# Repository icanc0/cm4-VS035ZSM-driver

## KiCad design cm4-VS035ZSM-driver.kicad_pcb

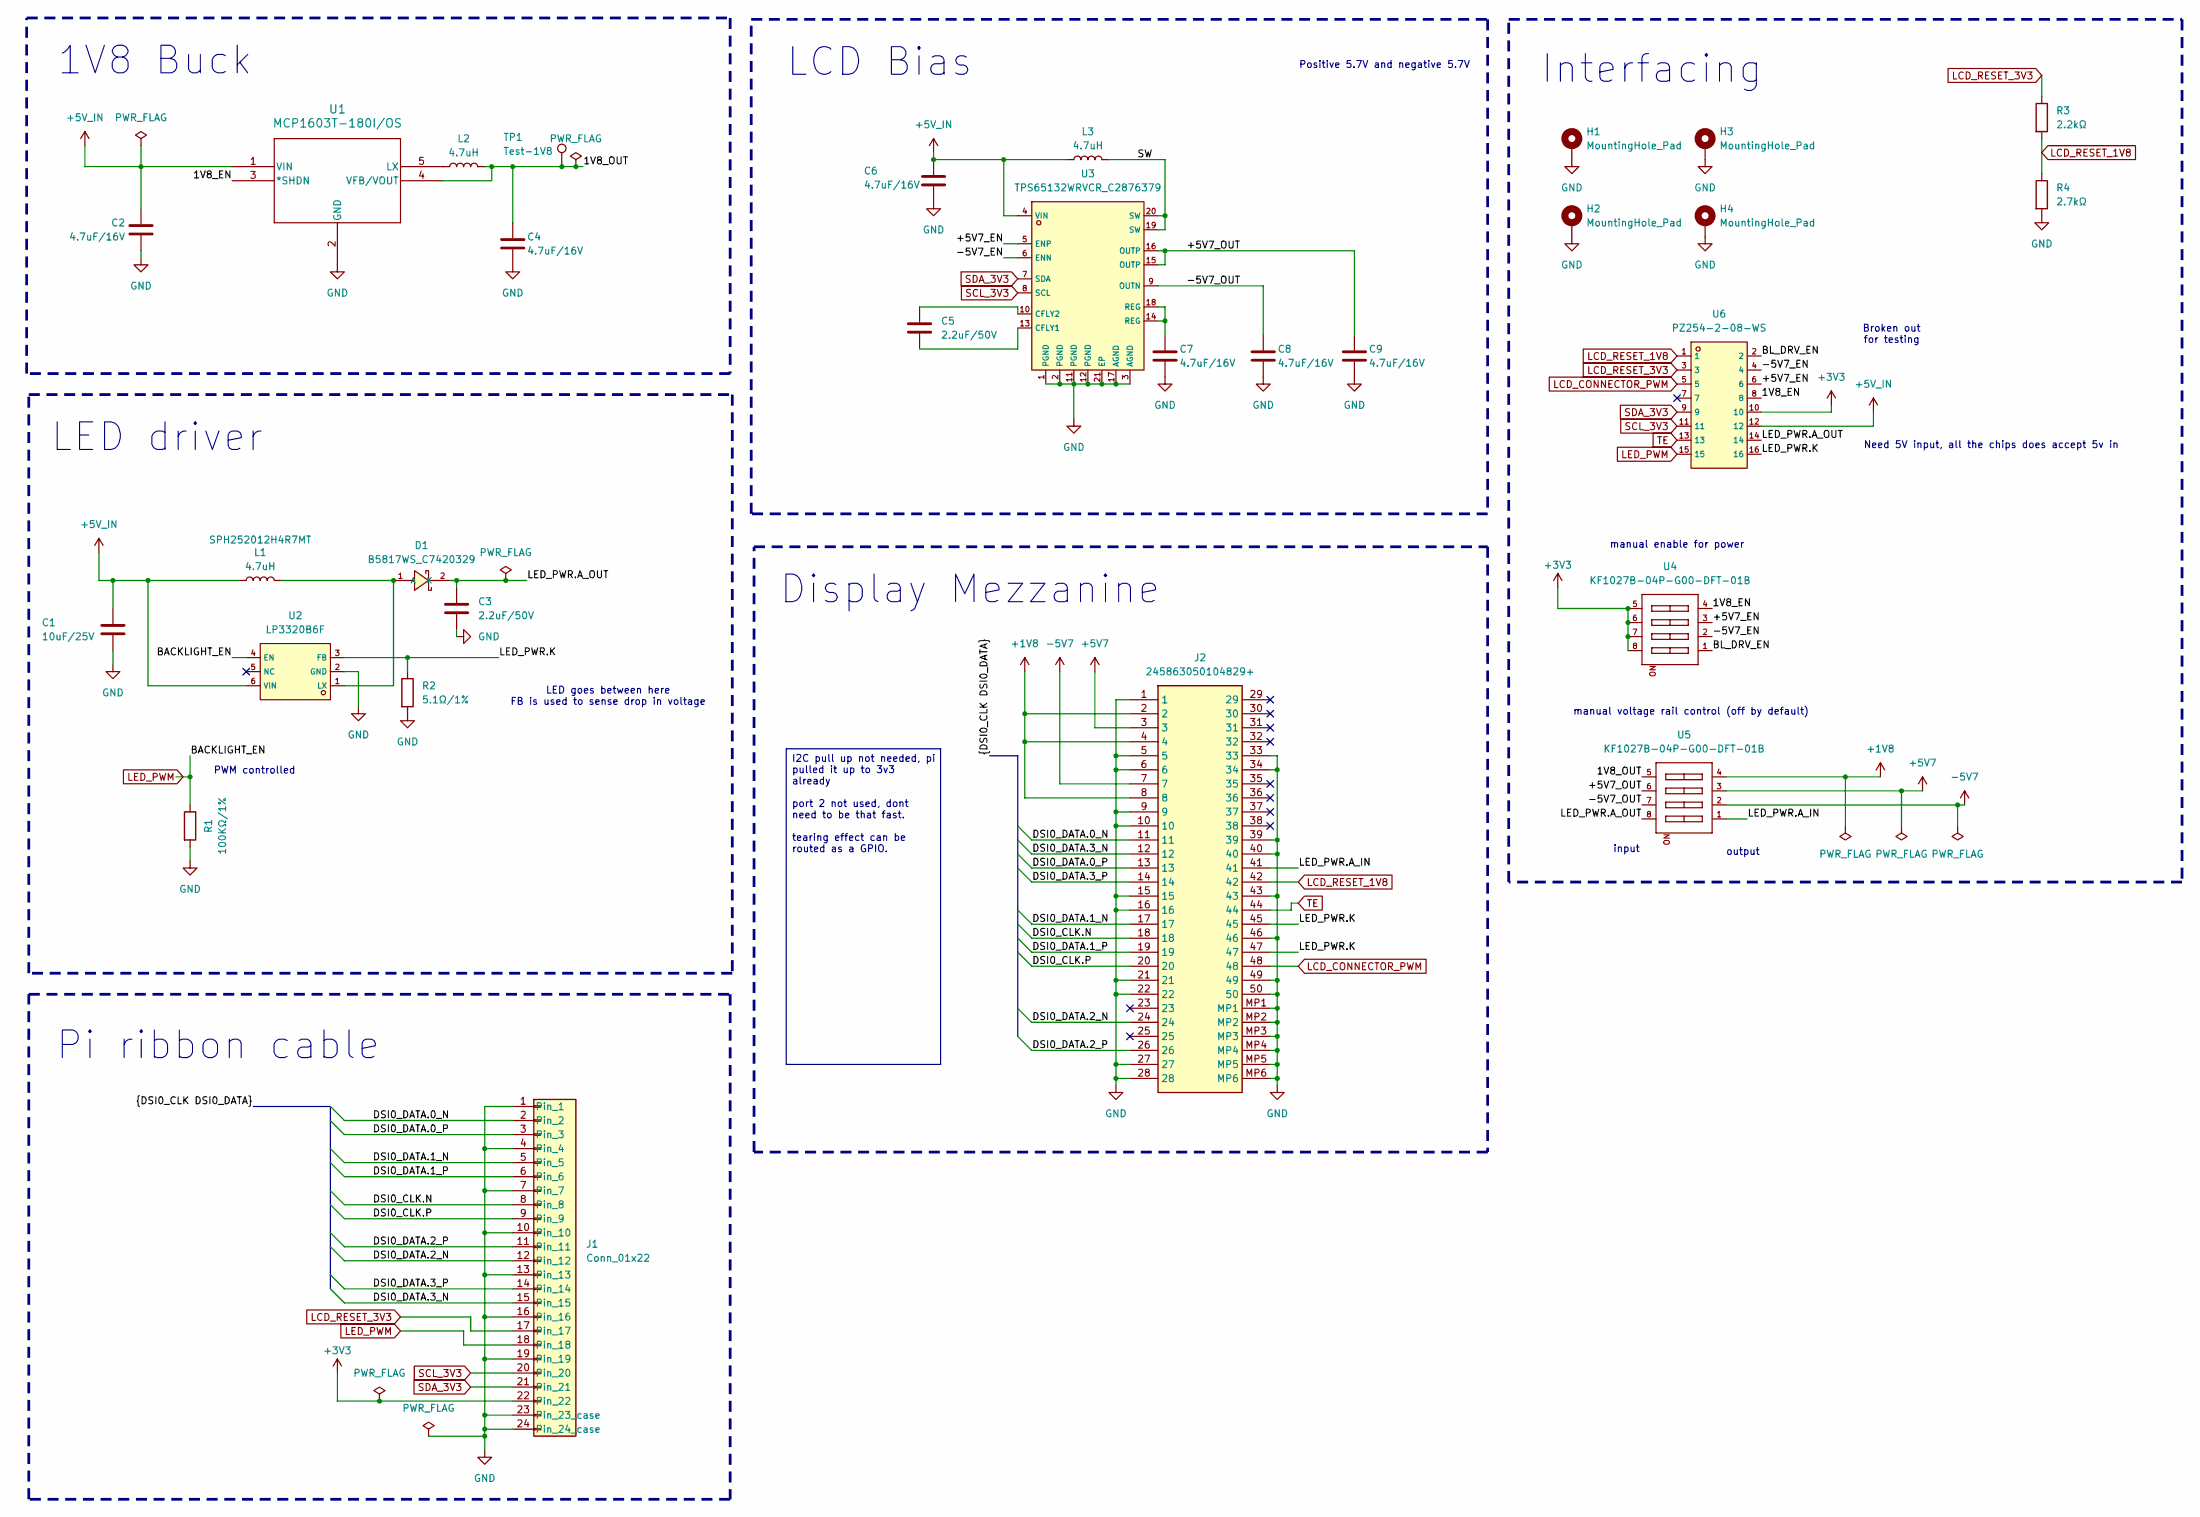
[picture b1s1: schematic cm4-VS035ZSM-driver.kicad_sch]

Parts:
C1: 10uF/25V; C_0603_1608Metric
C2, C4, C6, C7, C8, C9: 4.7uF/16V; C_0603_1608Metric
C3, C5: 2.2uF/50V; C_0805_2012Metric
D1: B5817WS_C7420329; SOD-323_L1.7-W1.3-LS2.5-FD; LCSC C7420329
H1, H2, H3, H4: MountingHole_Pad; MountingHole_3.2mm_M3_DIN965_Pad_TopBottom
J1: Conn_01x22; CON22_1X22_DRB_XF2C_TYC
J2: 245863050104829+; 245863050104829; Mouser Part Number 346-245863050104829+
L1, L2, L3: 4.7uH; IND-SMD_L2.5-W2.0_SPH252012
R1: 100KΩ/1%; R_0402_1005Metric
R2: 5.1Ω/1%; R_0805_2012Metric
R3: 2.2kΩ; R_0402_1005Metric
R4: 2.7kΩ; R_0603_1608Metric
TP1: Test-1V8; TestPoint_THTPad_D2.0mm_Drill1.0mm
U1: MCP1603T-180I/OS; TSOT5_MC_MCH
U2: LP3320B6F; SOT-23-6_L2.9-W1.6-P0.95-LS2.8-BL; LCSC C387699
U3: TPS65132WRVCR_C2876379; WQFN-20_L4.0-W3.0-P0.50-BL-EP; LCSC C2876379
U4, U5: KF1027B-04P-G00-DFT-01B; SW-SMD_KF1027B-04P-G00-DFT-01B; LCSC C976366
U6: PZ254-2-08-WS; HDR-SMD_16P-P2.54-H-M-R2-C8-W12.0-N; LCSC C5149358

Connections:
+1V8: J2.2, J2.4, J2.8, U5.4 (A4)
+3V3: J1.22, U4.5 (B4), U4.6 (B3), U4.7 (B2), U4.8 (B1), U6.10
+5V7: J2.3, U5.3 (A3)
+5V_IN: C1.2, C2.2, C6.1, L1.1, L3.1, U1.1 (VIN), U2.6 (VIN), U3.4 (VIN), U6.12
-5V7: J2.7, U5.2 (A2)
/1V8_EN: U1.3 (*SHDN), U4.4 (A4), U6.8
/1V8_OUT: C4.1, L2.2, TP1.1 (1_1), U1.4 (VFB/VOUT), U5.5 (B4)
/+5V7_EN: U3.5 (ENP), U4.3 (A3), U6.6
/+5V7_OUT: C9.1, U3.15 (OUTP), U3.16 (OUTP), U5.6 (B3)
/-5V7_EN: U3.6 (ENN), U4.2 (A2), U6.4
/-5V7_OUT: C8.1, U3.9 (OUTN), U5.7 (B2)
/BL_DRV_EN: U4.1 (A1), U6.2
/DSI0_CLK.N: J1.8, J2.18
/DSI0_CLK.P: J1.9, J2.20
/DSI0_DATA.0_N: J1.2, J2.11
/DSI0_DATA.0_P: J1.3, J2.13
/DSI0_DATA.1_N: J1.5, J2.17
/DSI0_DATA.1_P: J1.6, J2.19
/DSI0_DATA.2_N: J1.12, J2.24
/DSI0_DATA.2_P: J1.11, J2.26
/DSI0_DATA.3_N: J1.15, J2.12
/DSI0_DATA.3_P: J1.14, J2.14
/LED_PWR.A_IN: J2.41, U5.1 (A1)
/LED_PWR.A_OUT: C3.1, D1.2 (K), U5.8 (B1), U6.14
/LED_PWR.K: J2.45, J2.47, R2.1, U2.3 (FB), U6.16
/SW: L3.2, U3.19 (SW), U3.20 (SW)
GND: C1.1, C2.1, C3.2, C4.2, C6.2, C7.2, C8.2, C9.2, H1.1 (1_1), H2.1 (1_1), H3.1 (1_1), H4.1 (1_1), J1.1, J1.4, J1.7, J1.10, J1.13, J1.16, J1.19, J1.23 (Pin_23_case), J1.24 (Pin_24_case), J2.1, J2.5, J2.6, J2.9, J2.10, J2.15, J2.16, J2.21, J2.22, J2.27, J2.28, J2.33, J2.34, J2.39, J2.40, J2.43, J2.46, J2.49, J2.50, J2.MP1, J2.MP2, J2.MP3, J2.MP4, J2.MP5, J2.MP6, R1.2, R2.2, R4.2, U1.2 (GND), U2.2 (GND), U3.1 (PGND), U3.2 (PGND), U3.3 (AGND), U3.11 (PGND), U3.12 (PGND), U3.17 (AGND), U3.21 (EP)
LCD_CONNECTOR_PWM: J2.48, U6.5
LCD_RESET_1V8: J2.42, R3.2, R4.1, U6.1
LCD_RESET_3V3: J1.17, R3.1, U6.3
LED_PWM: J1.18, R1.1, U2.4 (EN), U6.15
unnamed: C7.1, U3.14 (REG), U3.18 (REG)
unnamed: D1.1 (A), L1.2, U2.1 (LX)
unnamed: L2.1, U1.5 (LX)
unnamed: C5.2, U3.13 (CFLY1)
unnamed: C5.1, U3.10 (CFLY2)
SCL_3V3: J1.20, U3.8 (SCL), U6.11
SDA_3V3: J1.21, U3.7 (SDA), U6.9
TE: J2.44, U6.13

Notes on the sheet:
manual enable for power
Display Mezzanine
Positive 5.7V and negative 5.7V
Pi ribbon cable
Broken out for testing
PWM controlled
LED driver
LED goes between here FB is used to sense drop in voltage
manual voltage rail control (off by default)
1V8 Buck
output
input
Need 5V input, all the chips does accept 5v in
Interfacing
LCD Bias
I2C pull up not needed, pi pulled it up to 3v3 already port 2 not used, dont need to be that fast. tearing effect can be routed as a GPIO.

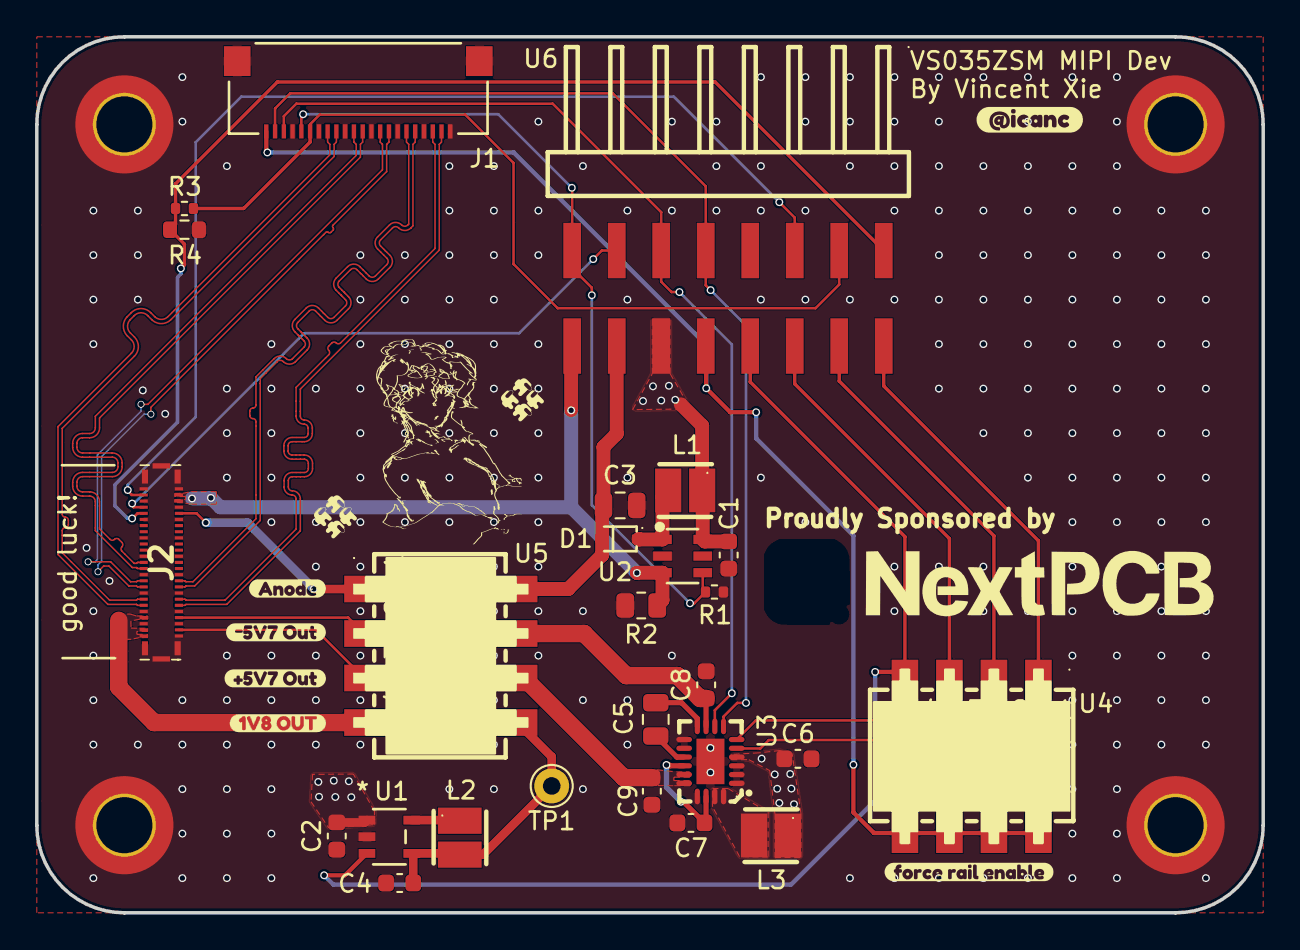
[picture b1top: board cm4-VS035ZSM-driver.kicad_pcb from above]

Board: 4 copper layers, 70.0 x 50.0 mm, 36 parts (0 on the bottom side), 39 nets.

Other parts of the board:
kibuzzard-685CA5ED: G***; kibuzzard-685CA5ED
kibuzzard-685CA6CA: G***; kibuzzard-685CA6CA
kibuzzard-685CA6D3: G***; kibuzzard-685CA6D3
kibuzzard-685CA724: G***; kibuzzard-685CA724
kibuzzard-68621EB5: G***; kibuzzard-68621EB5
kibuzzard-6996886F: G***; kibuzzard-6996886F

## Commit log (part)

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2024-09-19 progress fr
2024-10-05 essential routing done
2024-10-05 more routing
2025-06-13 1v8 buck and 4.7uh inductor
2025-06-26 init layout
2025-06-27 silkscreen
2025-06-30 board fabbed
2025-10-12 better driver design now that the cm5 has pin swapping support
2026-02-22 ok imma try kicad 10
2026-02-23 pre new revision
2026-02-23 finalized board before rounding corners
2026-02-23 done with v2
2026-03-09 Remove .history submodule
2026-05-21 gitignore lock files and .DS_Store
    Untrack the three ~*.kicad_*.lck files KiCad creates while a project is
    open, plus .DS_Store. Also strip the corrupted UTF-16 ". h i s t o r y"
    line from .gitignore and add explicit .history/ ignore.
2026-05-31 swap J2 connector to full-pads variant and use vias for routing
2026-06-07 update PCB, add design review notes + analysis dir
2026-06-12 Bump kicad-library to 5c8b195 (new header + KF1027B switch footprints)
